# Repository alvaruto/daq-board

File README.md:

# daq-board
USB Data Acquistion board with USART, SPI, I2C and nrf24l01 transceiver

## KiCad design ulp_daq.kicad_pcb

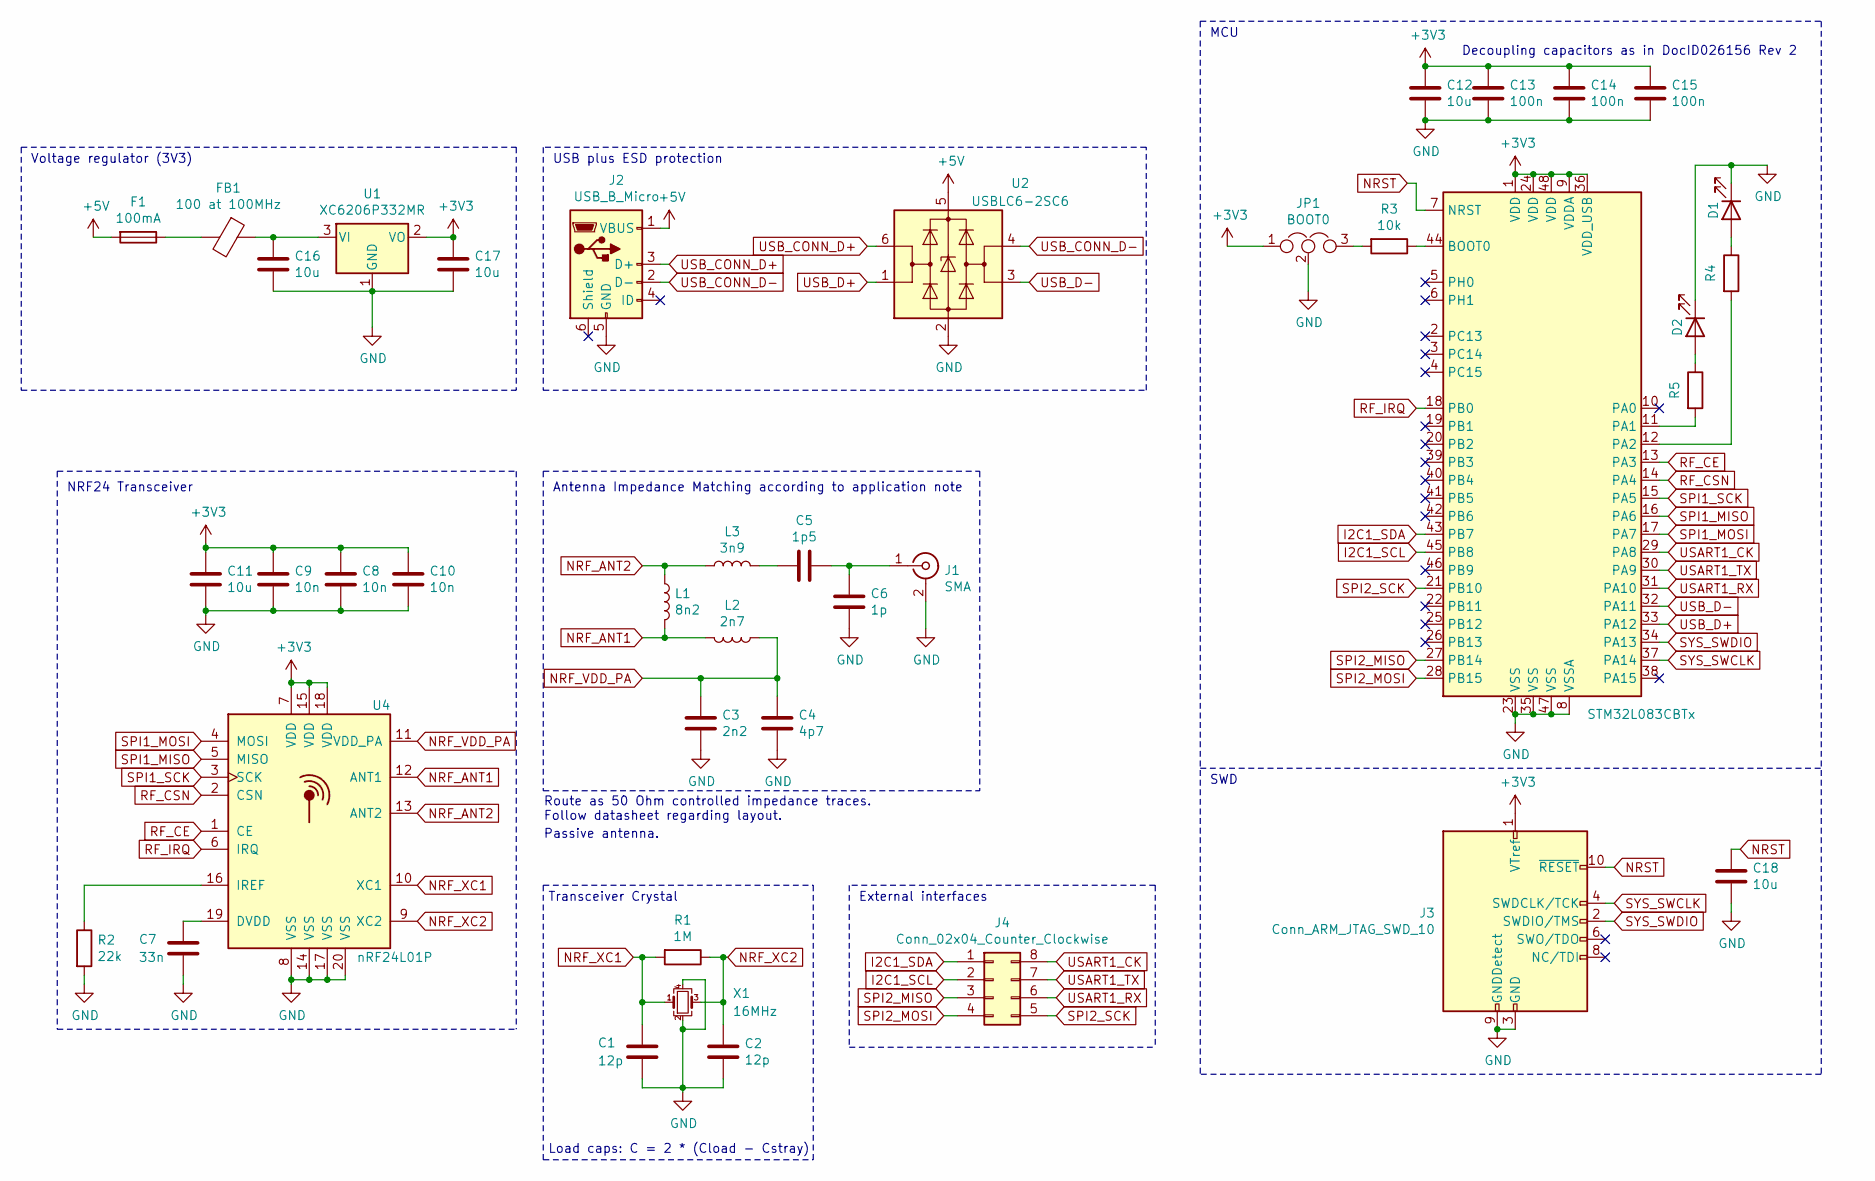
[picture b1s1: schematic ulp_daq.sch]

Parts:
C1, C2: 12p; C_0402_1005Metric
C3: 2n2; C_0402_1005Metric
C4: 4p7; C_0402_1005Metric
C5: 1p5; C_0402_1005Metric
C6: 1p; C_0402_1005Metric
C7: 33n; C_0402_1005Metric
C8, C9, C10: 10n; C_0402_1005Metric
C11, C12, C16, C17, C18: 10u; C_0603_1608Metric
C13, C14, C15: 100n; C_0402_1005Metric
D1: RX; LED_0603_1608Metric
D2: TX; LED_0603_1608Metric
F1: 100mA; Fuse_1206_3216Metric
FB1: 100 at 100MHz; L_0805_2012Metric
J1: SMA; SMA_Samtec_SMA-J-P-X-ST-EM1_EdgeMount
J2: USB_B_Micro; USB_Micro-B_Molex-105017-0001
J3: Conn_ARM_JTAG_SWD_10; PinHeader_2x05_P1.27mm_Vertical
J4: Conn_02x04_Counter_Clockwise; PinHeader_2x04_P1.27mm_Vertical
JP1: BOOT0; PinHeader_1x03_P1.27mm_Vertical
L1: 8n2; L_0402_1005Metric
L2: 2n7; L_0402_1005Metric
L3: 3n9; L_0402_1005Metric
R1: 1M; R_0402_1005Metric
R2: 22k; R_0402_1005Metric
R3: 10k; R_0402_1005Metric
R4, R5: 2k2; R_0402_1005Metric
U1: XC6206P332MR; SOT-23
U2: USBLC6-2SC6; SOT-23-6
U3: STM32L083CBTx; LQFP-48_7x7mm_P0.5mm
U4: nRF24L01P; QFN-20-1EP_4x4mm_P0.5mm_EP2.5x2.5mm
X1: 16MHz; Crystal_SMD_3225-4Pin_3.2x2.5mm

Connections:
+3V3: C8.1, C9.1, C10.1, C11.1, C12.1, C13.1, C14.1, C15.1, C17.1, J3.1 (VTref), JP1.1, U1.2 (VO), U3.1 (VDD), U3.9 (VDDA), U3.24 (VDD), U3.36 (VDD_USB), U3.48 (VDD), U4.7 (VDD), U4.15 (VDD), U4.18 (VDD)
+5V: F1.2, J2.1 (VBUS), U2.5 (VBUS)
GND: C1.2, C2.2, C3.1, C4.1, C6.1, C7.2, C8.2, C9.2, C10.2, C11.2, C12.2, C13.2, C14.2, C15.2, C16.2, C17.2, C18.2, D1.1 (K), D2.1 (K), J1.2 (Ext), J2.5 (GND), J3.3 (GND), J3.5 (GND), J3.9 (GNDDetect), JP1.2, R2.2, U1.1 (GND), U2.2 (GND), U3.8 (VSSA), U3.23 (VSS), U3.35 (VSS), U3.47 (VSS), U4.8 (VSS), U4.14 (VSS), U4.17 (VSS), U4.20 (VSS), X1.2, X1.4
I2C1_SCL: J4.2, U3.45 (PB8)
I2C1_SDA: J4.1, U3.43 (PB7)
NRF_ANT1: L1.2, L2.2, U4.12 (ANT1)
NRF_ANT2: L1.1, L3.1, U4.13 (ANT2)
NRF_VDD_PA: C3.2, C4.2, L2.1, U4.11 (VDD_PA)
NRF_XC1: C1.1, R1.2, U4.10 (XC1), X1.1
NRF_XC2: C2.1, R1.1, U4.9 (XC2), X1.3
NRST: C18.1, J3.10 (~RESET~), U3.7 (NRST)
unnamed: C5.1, C6.2, J1.1 (In)
unnamed: C5.2, L3.2
unnamed: C7.1, U4.19 (DVDD)
unnamed: C16.1, FB1.1, U1.3 (VI)
unnamed: D1.2 (A), R4.1
unnamed: D2.2 (A), R5.1
unnamed: F1.1, FB1.2
unnamed: JP1.3, R3.2
unnamed: R2.1, U4.16 (IREF)
unnamed: R3.1, U3.44 (BOOT0)
unnamed: R4.2, U3.12 (PA2)
unnamed: R5.2, U3.11 (PA1)
RF_CE: U3.13 (PA3), U4.1 (CE)
RF_CSN: U3.14 (PA4), U4.2 (CSN)
RF_IRQ: U3.18 (PB0), U4.6 (IRQ)
SPI1_MISO: U3.16 (PA6), U4.5 (MISO)
SPI1_MOSI: U3.17 (PA7), U4.4 (MOSI)
SPI1_SCK: U3.15 (PA5), U4.3 (SCK)
SPI2_MISO: J4.3, U3.27 (PB14)
SPI2_MOSI: J4.4, U3.28 (PB15)
SPI2_SCK: J4.5, U3.21 (PB10)
SYS_SWCLK: J3.4 (SWDCLK/TCK), U3.37 (PA14)
SYS_SWDIO: J3.2 (SWDIO/TMS), U3.34 (PA13)
USART1_CK: J4.8, U3.29 (PA8)
USART1_RX: J4.6, U3.31 (PA10)
USART1_TX: J4.7, U3.30 (PA9)
USB_CONN_D+: J2.3 (D+), U2.6 (I/O1)
USB_CONN_D-: J2.2 (D-), U2.4 (I/O2)
USB_D+: U2.1 (I/O1), U3.33 (PA12)
USB_D-: U2.3 (I/O2), U3.32 (PA11)

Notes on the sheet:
Decoupling capacitors as in DocID026156 Rev 2
MCU
SWD
Voltage regulator (3V3)
Load caps: C = 2 * (Cload - Cstray)
NRF24 Transceiver
Transceiver Crystal
Antenna Impedance Matching according to application note
Route as 50 Ohm controlled impedance traces. Follow datasheet regarding layout.
Passive antenna.
USB plus ESD protection
External interfaces

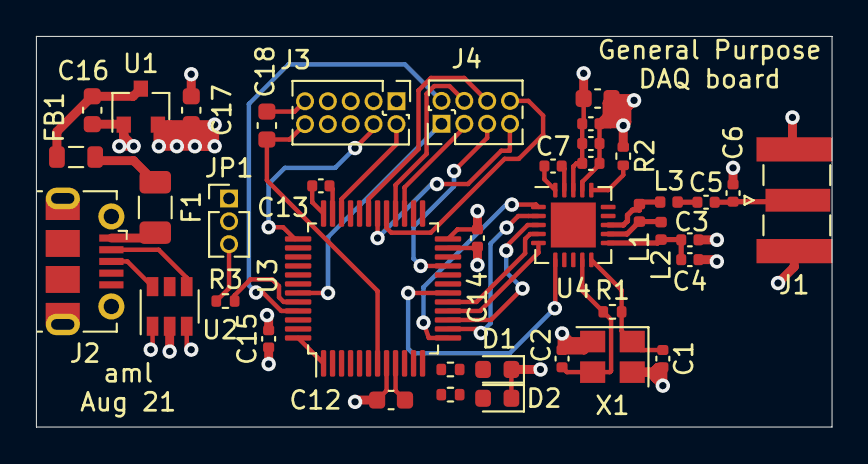
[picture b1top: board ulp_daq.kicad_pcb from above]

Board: 4 copper layers, 44.2 x 21.7 mm, 40 parts (0 on the bottom side), 41 nets.

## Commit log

2021-08-13 Initial commit. Work in progress
